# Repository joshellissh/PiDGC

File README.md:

# PiDGC v2
Raspberry Pi based Digital Gauge Cluster by Josh Ellis / josh@ellis.sh

**Please Note: This library is designed for the Raspberry Pi 3B, a custom built PCB, and a 1280x480 display. It
will look weird on other displays and won't function without those components.**

You can see what it does here: https://www.youtube.com/watch?v=zrCutGj2v5M

### Update Information
This repository is a total rewrite of the PiDGC codebase. The kotlin hardware interface has 
been removed, and all code is now in either the microcontroller (Teensy 4.1) or the Qt 
application running on the RPi. These changes were made to simplify the system and significantly 
shorten the boot time.

### Acknowledgements
In order to reduce the boot time significantly, this version of the gauge cluster uses [buildroot](https://buildroot.org/).
A fork of the [configuration](https://github.com/furkantokac/buildroot) made by [Furkan Tokaç](https://furkantokac.com/rpi3-fast-boot-less-than-2-seconds/) 
is the basis of this build, so many thanks for the reduced boot time go to him! Please go and check out his work, 
it's great.

### Software Steps
Since this is a buildroot build and no binaries are provided, you must build the image for the Raspberry Pi 3 yourself.
This isn't a complicated process, but does require either a Linux system or WSL2.

**These are high level steps only. If you have questions about how to do any step, please Google it.**

1. `cd` into the `buildroot` directory
2. `make pidgc_defconfig`
3. `make -j8`
4. `./build-rpi3-qt.sh`
5. Setup Qt Creator to use the qmake found in `buildroot/output/qt/qt-everywhere-src-*/aaaout/bin/qmake` and compile for the Raspberyr Pi 3.
6. Open `source/display` in Qt Creator and compile for RPi3.
7. Run `make -j8` again. This should pull in the `rpi3-display/display` binary and create the `sdcard.img` in `buildroot/output/images/sdcard.img`.
8. Burn the image file to a micro SD card.
9. All done!

### Custom PCB
The PCB was designed in EAGLE, and is located in `files/PiDGCv2-pcb`

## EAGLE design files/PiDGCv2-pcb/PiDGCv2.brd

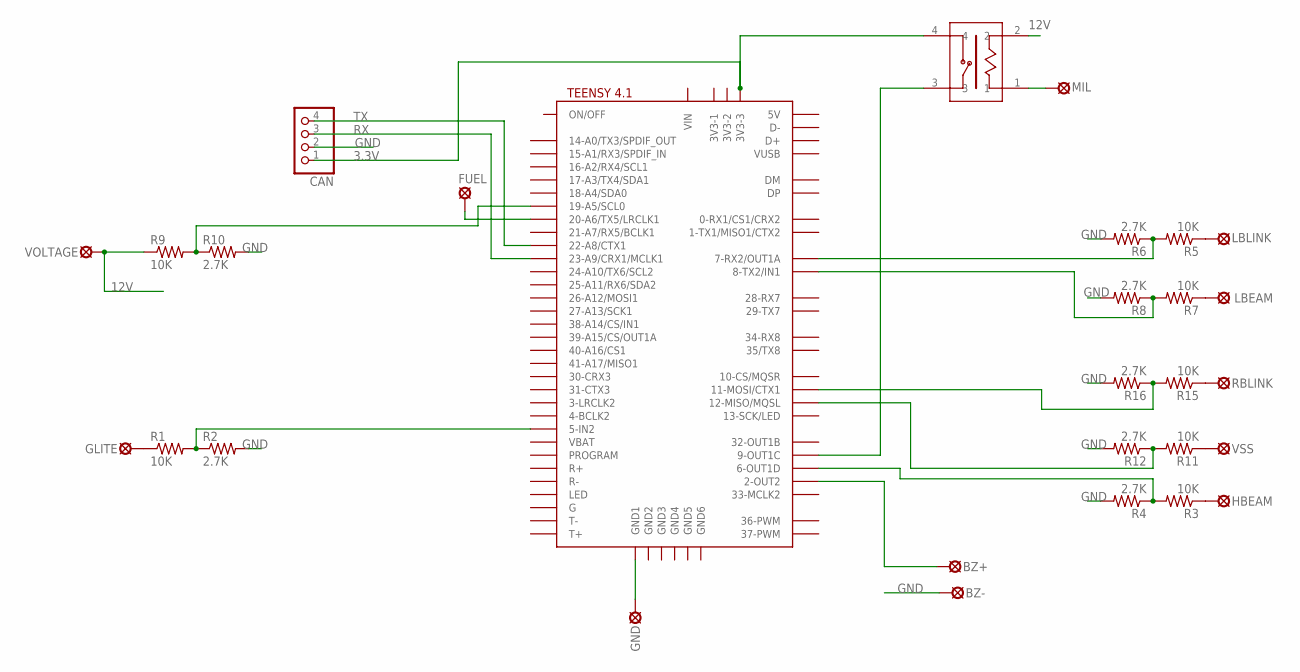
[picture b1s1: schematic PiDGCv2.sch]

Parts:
BZ+: LSP10
BZ-: LSP10
CAN: PINHD-1X4; 1X04
FUEL: LSP10
GLITE: LSP10
GND: LSP10
HBEAM: LSP10
LBEAM: LSP10
LBLINK: LSP10
MIL: LSP10
MIL_RELAY: BR-1050-VP; RELAY
R1, R3, R5, R7, R9, R11, R15: 10K; 0204/7
R2, R4, R6, R8, R10, R12, R16: 2.7K; 0204/7
RBLINK: LSP10
U$1: TEENSY41
VOLTAGE: LSP10
VSS: LSP10

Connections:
3.3V: CAN.1, MIL_RELAY.4, U$1.3V3-3
12V: MIL_RELAY.2, R9.1, VOLTAGE.MP; also elsewhere on the board
GND: BZ-.MP, CAN.2, GND.MP, R2.2, R4.2, R6.2, R8.2, R10.2, R12.2, R16.2, U$1.GND1
unnamed: R3.2, R4.1, U$1.6-OUT1D
unnamed: R1.2, R2.1, U$1.5-IN2
unnamed: GLITE.MP, R1.1
unnamed: HBEAM.MP, R3.1
unnamed: R5.2, R6.1, U$1.7-RX2/OUT1A
unnamed: LBLINK.MP, R5.1
unnamed: R7.2, R8.1, U$1.8-TX2/IN2 (8-TX2/IN1)
unnamed: LBEAM.MP, R7.1
unnamed: FUEL.MP, U$1.20-A6/TX5/LRCLK1
unnamed: R9.2, R10.1, U$1.19-A5/SCL0
unnamed: R11.2, R12.1, U$1.12-MISO/MQSL
unnamed: R11.1, VSS.MP
unnamed: R15.2, R16.1, U$1.11-MOSI/CTX1
unnamed: R15.1, RBLINK.MP
unnamed: MIL.MP, MIL_RELAY.1
unnamed: MIL_RELAY.3, U$1.9-OUT1C
unnamed: BZ+.MP, U$1.2-OUT2
RX: CAN.3, U$1.23-A9/CRX1/MCLK1
TX: CAN.4, U$1.22-A8/CTX1

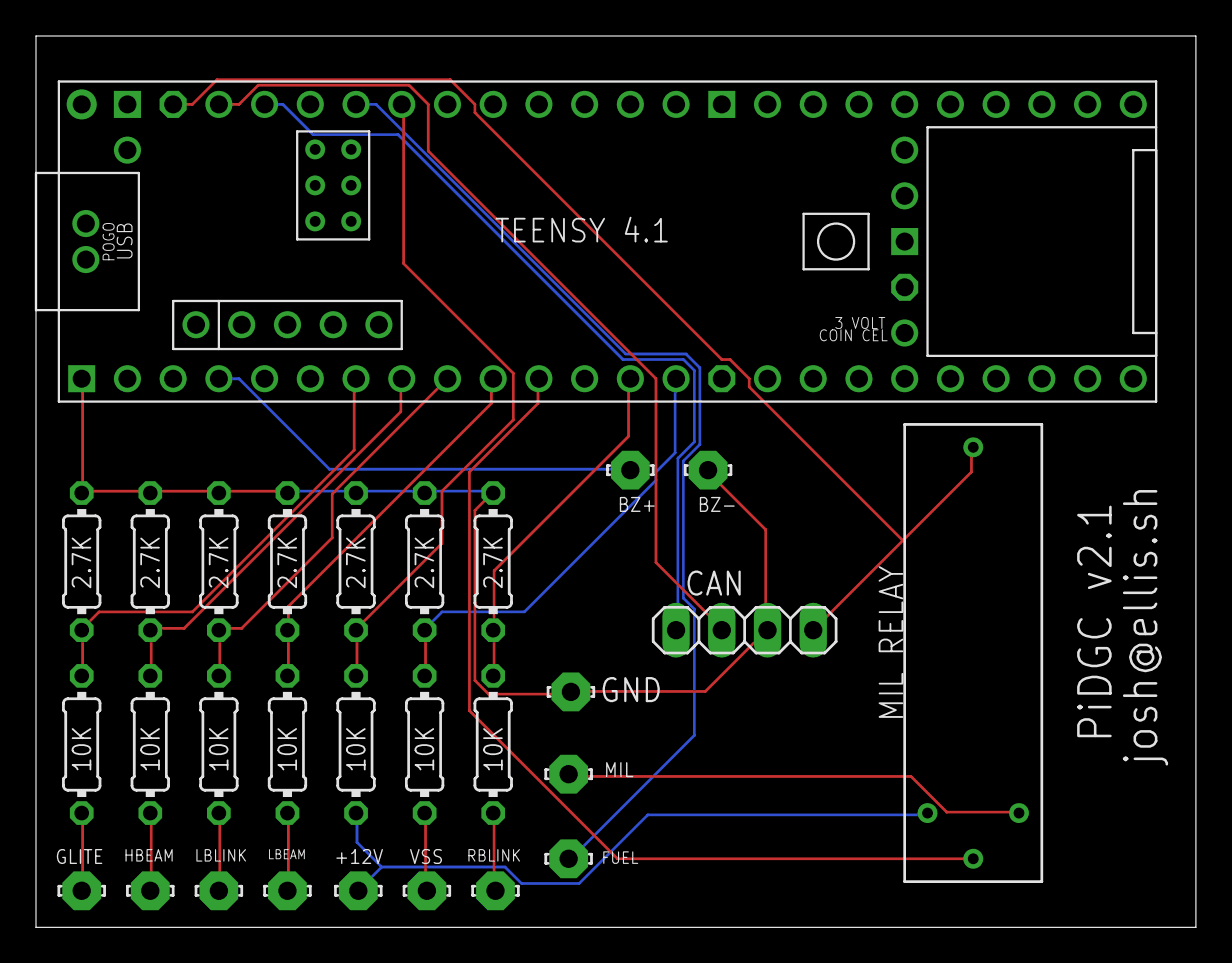
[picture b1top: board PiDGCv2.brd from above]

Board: 2 copper layers, 64.4 x 49.5 mm, 29 parts (0 on the bottom side), 22 nets.

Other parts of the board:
+12V: LSP10

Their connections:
12V: +12V.MP; also elsewhere on the board

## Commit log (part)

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2022-04-01 Initial v2 commit
2022-05-31 Process events
2022-05-31 Add status log line
2022-06-01 Update graphic and add font
2022-06-01 Remove wrong files
2022-06-01 Remove intellij directory
2022-06-03 uC code updates
2022-06-14 Lots of work
2022-07-20 Update all the things
2022-07-20 Update all the things!
2022-07-20 Update default confis
2022-07-20 Add support for teensy
2022-07-21 Update config for proper display
2022-07-21 Bug fixes
2022-07-28 File updates
2022-07-28 Update README and add PCB files
2023-01-27 Updates to display and microcontroller
2023-01-27 Send speed to ECU via canbus
2023-01-27 Update blinker frequency and send correct MPH to ECU
2023-02-05 Uncomment line that was accidentally left commented
2023-02-19 Add datalogging capability
